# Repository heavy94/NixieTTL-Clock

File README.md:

# NixieTTL Clock
Tabletop digital clock built using TTL/CMOS logic ICs with a Nixie tube display.

**TODO**
- PCB layout and design.
- Test High Voltage power supply.
- Test need for base resistor on the cathode drivers.
- Test and tune blanking time generator.

**References**

This design is inspired by the following projects and resources:
- https://0x7d.com/2017/nixie-tube-clock/
- https://threeneurons.wordpress.com/nixie-power-supply/nixie-clock-kit-microcontroller/
- https://threeneurons.wordpress.com/nixie-power-supply/nixie-clock-kit-microcontroller/ghosting-due-to-transients/
- https://threeneurons.wordpress.com/nixie-power-supply/hv-supply-kit/

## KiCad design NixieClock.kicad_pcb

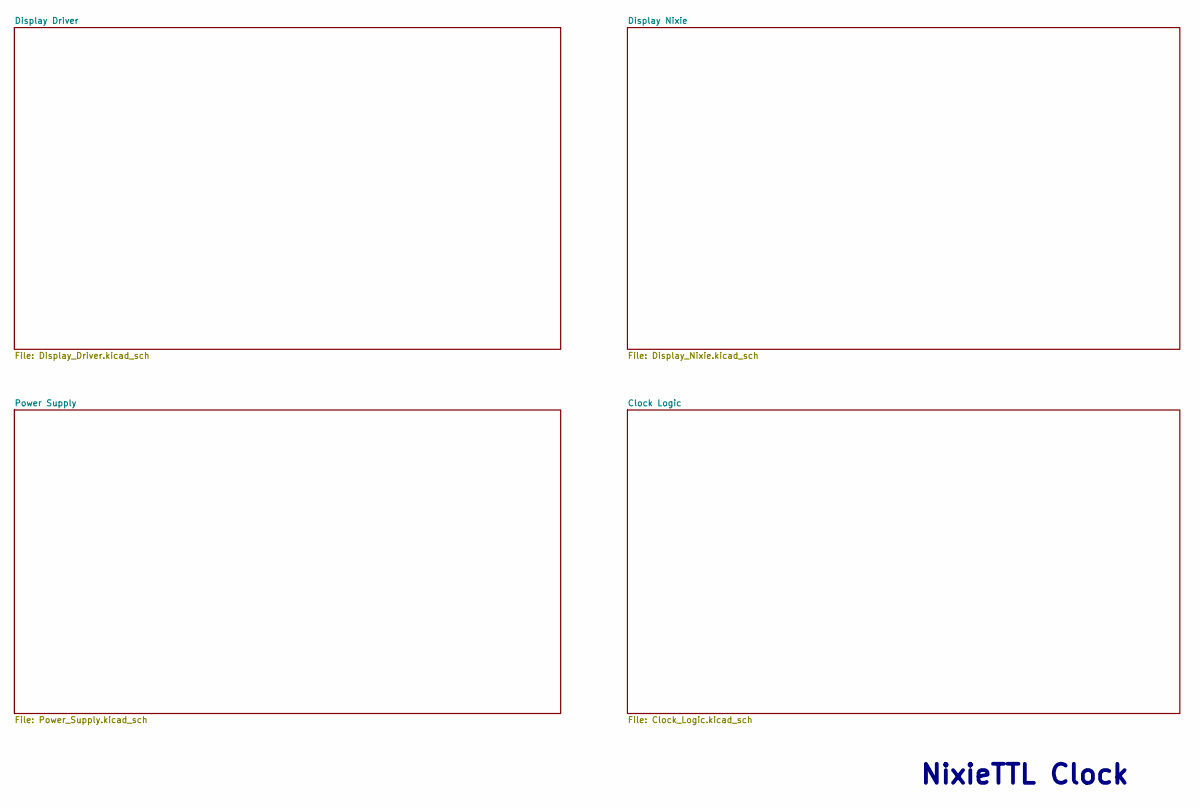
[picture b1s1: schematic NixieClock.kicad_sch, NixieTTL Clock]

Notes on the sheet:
NixieTTL Clock

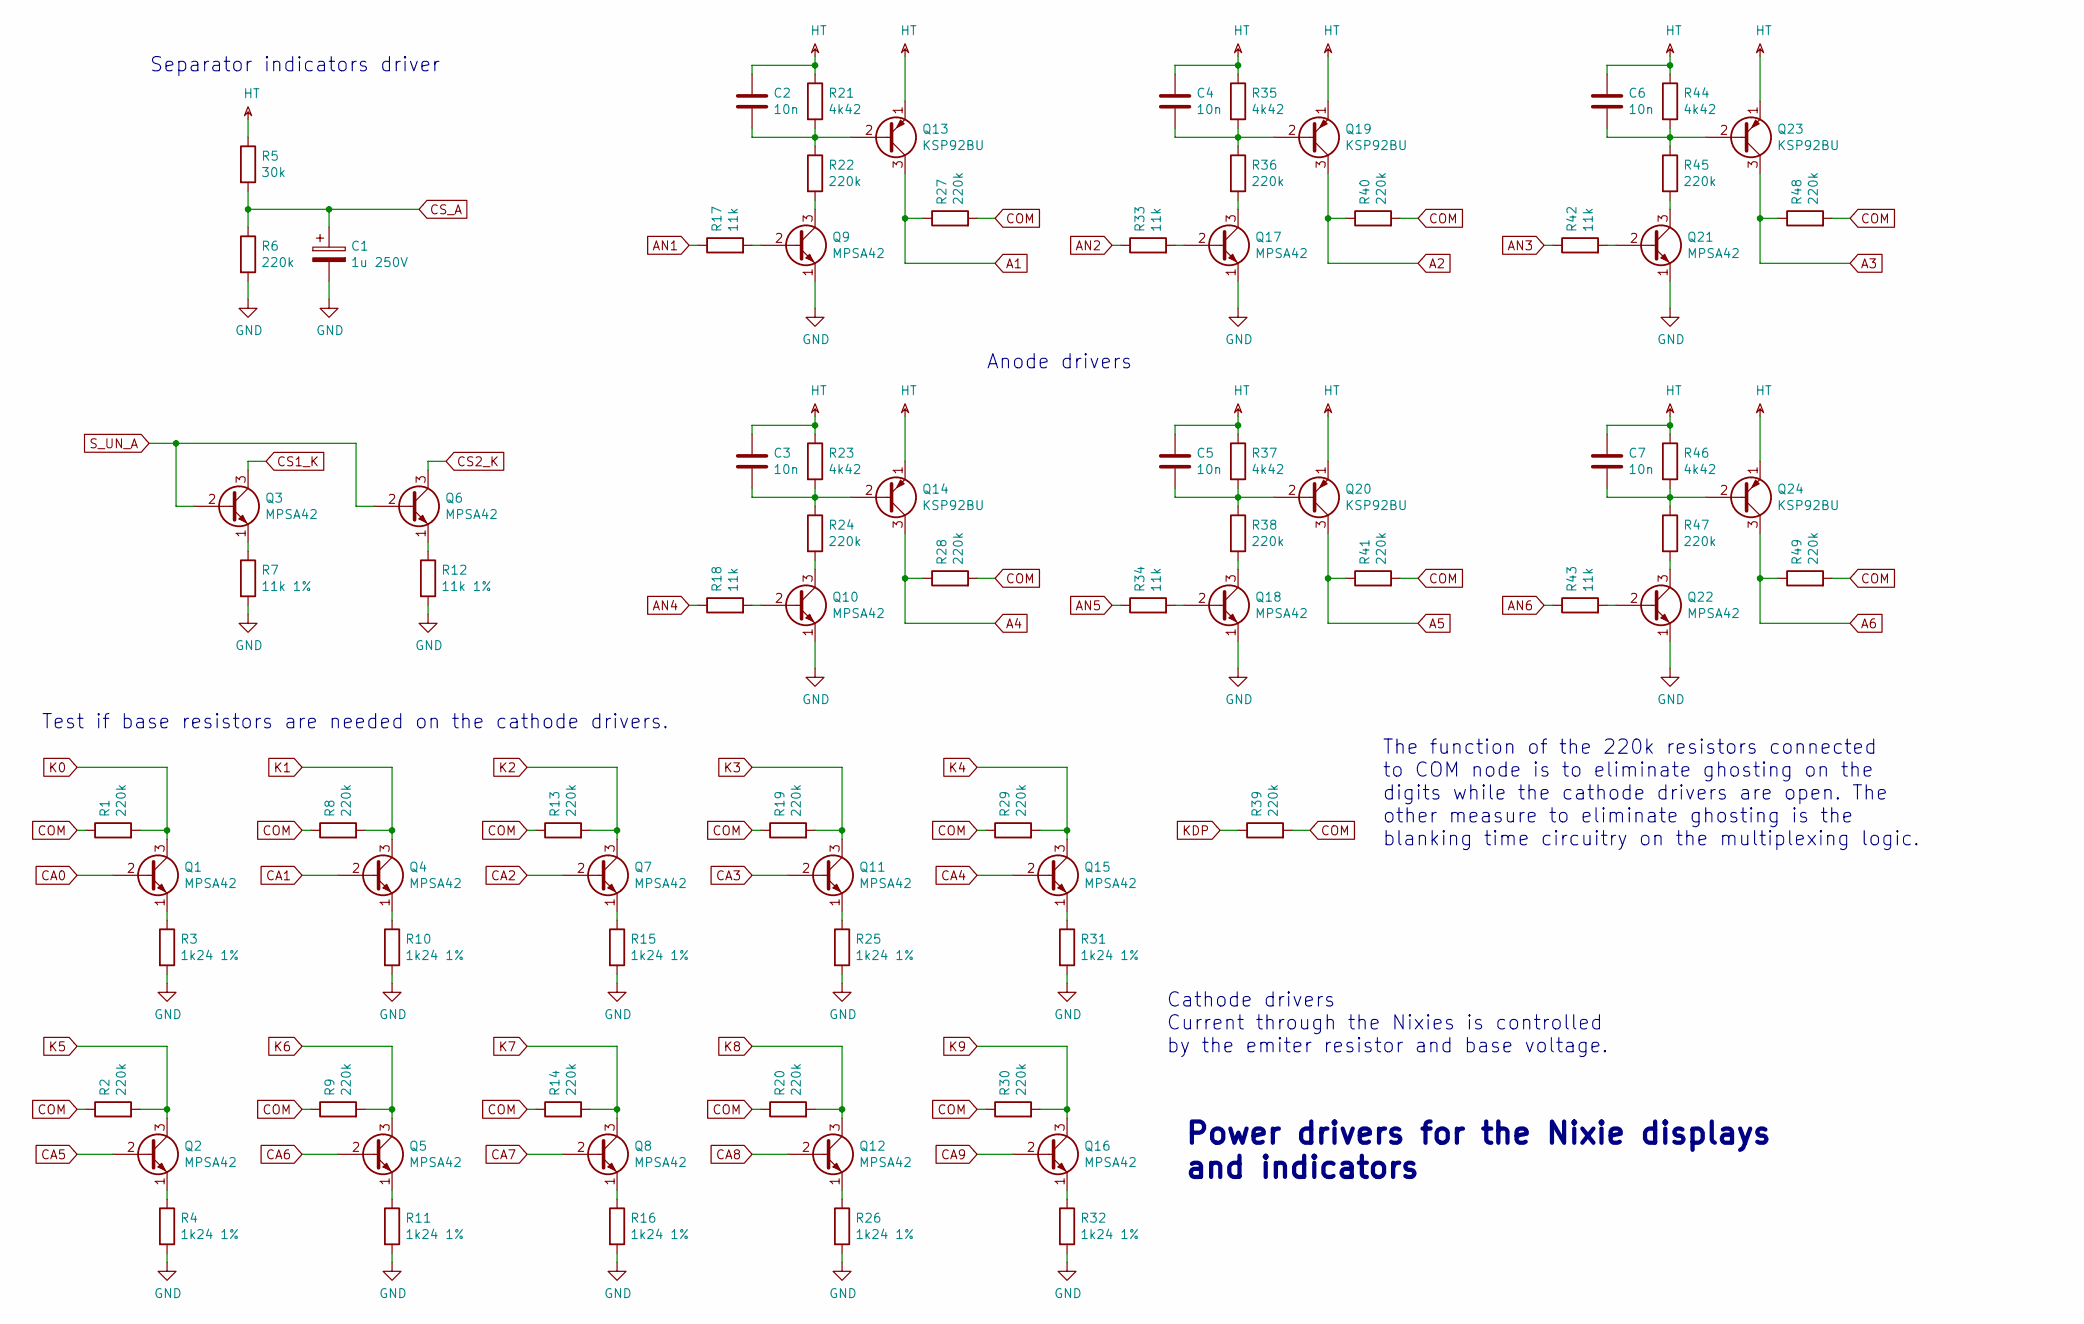
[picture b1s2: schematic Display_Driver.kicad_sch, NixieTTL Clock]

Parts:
C1: 1u 250V; CP_Radial_D8.0mm_P3.80mm
C2, C3, C4, C5, C6, C7: 10n; C_Rect_L7.0mm_W2.5mm_P5.00mm
Q1, Q2, Q3, Q4, Q5, Q6, Q7, Q8, Q9, Q10, Q11, Q12, Q15, Q16, Q17, Q18, Q21, Q22: MPSA42; TO-92_Inline_Wide
Q13, Q14, Q19, Q20, Q23, Q24: KSP92BU; TO-92_Inline_Wide
R1, R2, R6, R8, R9, R13, R14, R19, R20, R22, R24, R27, R28, R29, R30, R36, R38, R39, R40, R41, R45, R47, R48, R49: 220k; R_Axial_DIN0207_L6.3mm_D2.5mm_P10.16mm_Horizontal
R3, R4, R10, R11, R15, R16, R25, R26, R31, R32: 1k24 1%; R_Axial_DIN0207_L6.3mm_D2.5mm_P10.16mm_Horizontal
R5: 30k; R_Axial_DIN0207_L6.3mm_D2.5mm_P10.16mm_Horizontal
R7, R12: 11k 1%; R_Axial_DIN0207_L6.3mm_D2.5mm_P10.16mm_Horizontal
R17, R18, R33, R34, R42, R43: 11k; R_Axial_DIN0207_L6.3mm_D2.5mm_P10.16mm_Horizontal
R21, R23, R35, R37, R44, R46: 4k42; R_Axial_DIN0207_L6.3mm_D2.5mm_P10.16mm_Horizontal

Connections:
A1: Q13.3 (C), R27.1; also elsewhere on the board
A2: Q19.3 (C), R40.1; also elsewhere on the board
A3: Q23.3 (C), R48.1; also elsewhere on the board
A4: Q14.3 (C), R28.1; also elsewhere on the board
A5: Q20.3 (C), R41.1; also elsewhere on the board
A6: Q24.3 (C), R49.1; also elsewhere on the board
AN1: R17.1; also elsewhere on the board
AN2: R33.1; also elsewhere on the board
AN3: R42.1; also elsewhere on the board
AN4: R18.1; also elsewhere on the board
AN5: R34.1; also elsewhere on the board
AN6: R43.1; also elsewhere on the board
CA0: Q1.2 (B); also elsewhere on the board
CA1: Q4.2 (B); also elsewhere on the board
CA2: Q7.2 (B); also elsewhere on the board
CA3: Q11.2 (B); also elsewhere on the board
CA4: Q15.2 (B); also elsewhere on the board
CA5: Q2.2 (B); also elsewhere on the board
CA6: Q5.2 (B); also elsewhere on the board
CA7: Q8.2 (B); also elsewhere on the board
CA8: Q12.2 (B); also elsewhere on the board
CA9: Q16.2 (B); also elsewhere on the board
COM: R1.1, R2.1, R8.1, R9.1, R13.1, R14.1, R19.1, R20.1, R27.2, R28.2, R29.1, R30.1, R39.2, R40.2, R41.2, R48.2, R49.2
CS1_K: Q3.3 (C); also elsewhere on the board
CS2_K: Q6.3 (C); also elsewhere on the board
CS_A: C1.1, R5.2, R6.1; also elsewhere on the board
GND: C1.2, Q9.1 (E), Q10.1 (E), Q17.1 (E), Q18.1 (E), Q21.1 (E), Q22.1 (E), R3.2, R4.2, R6.2, R7.2, R10.2, R11.2, R12.2, R15.2, R16.2, R25.2, R26.2, R31.2, R32.2; also elsewhere on the board
HT: C2.1, C3.1, C4.1, C5.1, C6.1, C7.1, Q13.1 (E), Q14.1 (E), Q19.1 (E), Q20.1 (E), Q23.1 (E), Q24.1 (E), R5.1, R21.1, R23.1, R35.1, R37.1, R44.1, R46.1; also elsewhere on the board
K0: Q1.3 (C), R1.2; also elsewhere on the board
K1: Q4.3 (C), R8.2; also elsewhere on the board
K2: Q7.3 (C), R13.2; also elsewhere on the board
K3: Q11.3 (C), R19.2; also elsewhere on the board
K4: Q15.3 (C), R29.2; also elsewhere on the board
K5: Q2.3 (C), R2.2; also elsewhere on the board
K6: Q5.3 (C), R9.2; also elsewhere on the board
K7: Q8.3 (C), R14.2; also elsewhere on the board
K8: Q12.3 (C), R20.2; also elsewhere on the board
K9: Q16.3 (C), R30.2; also elsewhere on the board
KDP: R39.1; also elsewhere on the board
unnamed: C2.2, Q13.2 (B), R21.2, R22.1
unnamed: C3.2, Q14.2 (B), R23.2, R24.1
unnamed: C4.2, Q19.2 (B), R35.2, R36.1
unnamed: C5.2, Q20.2 (B), R37.2, R38.1
unnamed: C6.2, Q23.2 (B), R44.2, R45.1
unnamed: C7.2, Q24.2 (B), R46.2, R47.1
unnamed: Q1.1 (E), R3.1
unnamed: Q2.1 (E), R4.1
unnamed: Q3.1 (E), R7.1
unnamed: Q4.1 (E), R10.1
unnamed: Q5.1 (E), R11.1
unnamed: Q6.1 (E), R12.1
unnamed: Q7.1 (E), R15.1
unnamed: Q8.1 (E), R16.1
unnamed: Q9.2 (B), R17.2
unnamed: Q9.3 (C), R22.2
unnamed: Q10.2 (B), R18.2
unnamed: Q10.3 (C), R24.2
unnamed: Q11.1 (E), R25.1
unnamed: Q12.1 (E), R26.1
unnamed: Q15.1 (E), R31.1
unnamed: Q16.1 (E), R32.1
unnamed: Q17.2 (B), R33.2
unnamed: Q17.3 (C), R36.2
unnamed: Q18.2 (B), R34.2
unnamed: Q18.3 (C), R38.2
unnamed: Q21.2 (B), R42.2
unnamed: Q21.3 (C), R45.2
unnamed: Q22.2 (B), R43.2
unnamed: Q22.3 (C), R47.2
S_UN_A: Q3.2 (B), Q6.2 (B); also elsewhere on the board

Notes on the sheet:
Test if base resistors are needed on the cathode drivers.
The function of the 220k resistors connected to COM node is to eliminate ghosting on the digits while the cathode drivers are open. The other measure to eliminate ghosting is the blanking time circuitry on the multiplexing logic.
Separator indicators driver
Power drivers for the Nixie displays and indicators
Cathode drivers Current through the Nixies is controlled by the emiter resistor and base voltage.
Anode drivers

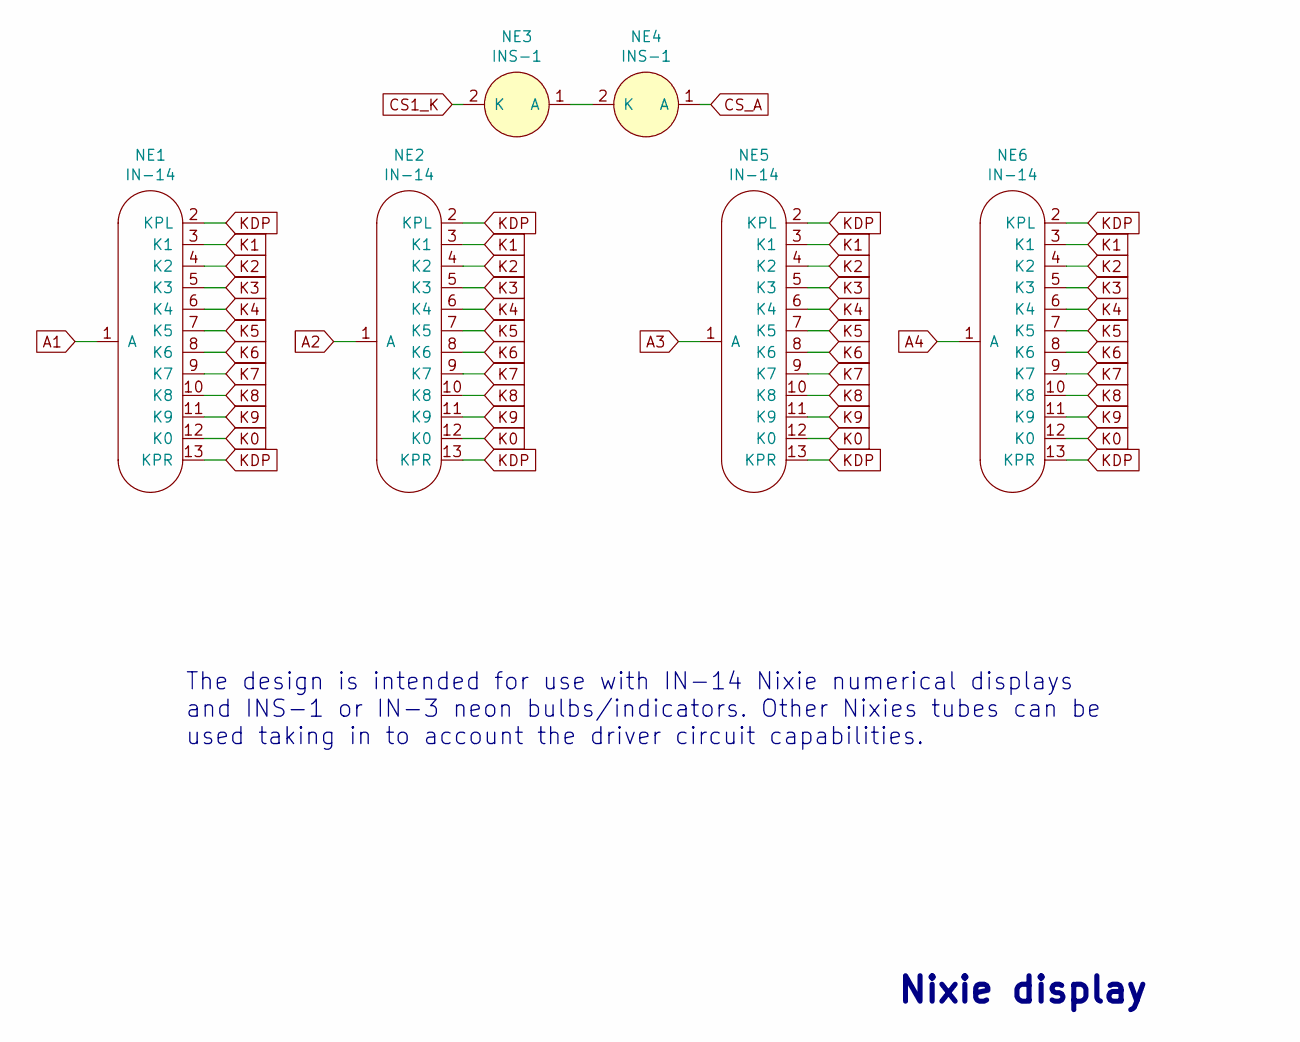
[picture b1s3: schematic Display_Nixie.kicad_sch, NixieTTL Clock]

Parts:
NE1, NE2, NE5, NE6: IN-14
NE3, NE4: INS-1; PinSocket_1x02_P2.54mm_Vertical

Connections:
A1: NE1.1 (A); also elsewhere on the board
A2: NE2.1 (A); also elsewhere on the board
A3: NE5.1 (A); also elsewhere on the board
A4: NE6.1 (A); also elsewhere on the board
CS1_K: NE3.2 (K); also elsewhere on the board
CS_A: NE4.1 (A); also elsewhere on the board
K0: NE1.12 (K0), NE2.12 (K0), NE5.12 (K0), NE6.12 (K0); also elsewhere on the board
K1: NE1.3 (K1), NE2.3 (K1), NE5.3 (K1), NE6.3 (K1); also elsewhere on the board
K2: NE1.4 (K2), NE2.4 (K2), NE5.4 (K2), NE6.4 (K2); also elsewhere on the board
K3: NE1.5 (K3), NE2.5 (K3), NE5.5 (K3), NE6.5 (K3); also elsewhere on the board
K4: NE1.6 (K4), NE2.6 (K4), NE5.6 (K4), NE6.6 (K4); also elsewhere on the board
K5: NE1.7 (K5), NE2.7 (K5), NE5.7 (K5), NE6.7 (K5); also elsewhere on the board
K6: NE1.8 (K6), NE2.8 (K6), NE5.8 (K6), NE6.8 (K6); also elsewhere on the board
K7: NE1.9 (K7), NE2.9 (K7), NE5.9 (K7), NE6.9 (K7); also elsewhere on the board
K8: NE1.10 (K8), NE2.10 (K8), NE5.10 (K8), NE6.10 (K8); also elsewhere on the board
K9: NE1.11 (K9), NE2.11 (K9), NE5.11 (K9), NE6.11 (K9); also elsewhere on the board
KDP: NE1.2 (KPL), NE1.13 (KPR), NE2.2 (KPL), NE2.13 (KPR), NE5.2 (KPL), NE5.13 (KPR), NE6.2 (KPL), NE6.13 (KPR); also elsewhere on the board
unnamed: NE3.1 (A), NE4.2 (K)

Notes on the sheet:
Nixie display
The design is intended for use with IN-14 Nixie numerical displays and INS-1 or IN-3 neon bulbs/indicators. Other Nixies tubes can be used taking in to account the driver circuit capabilities.

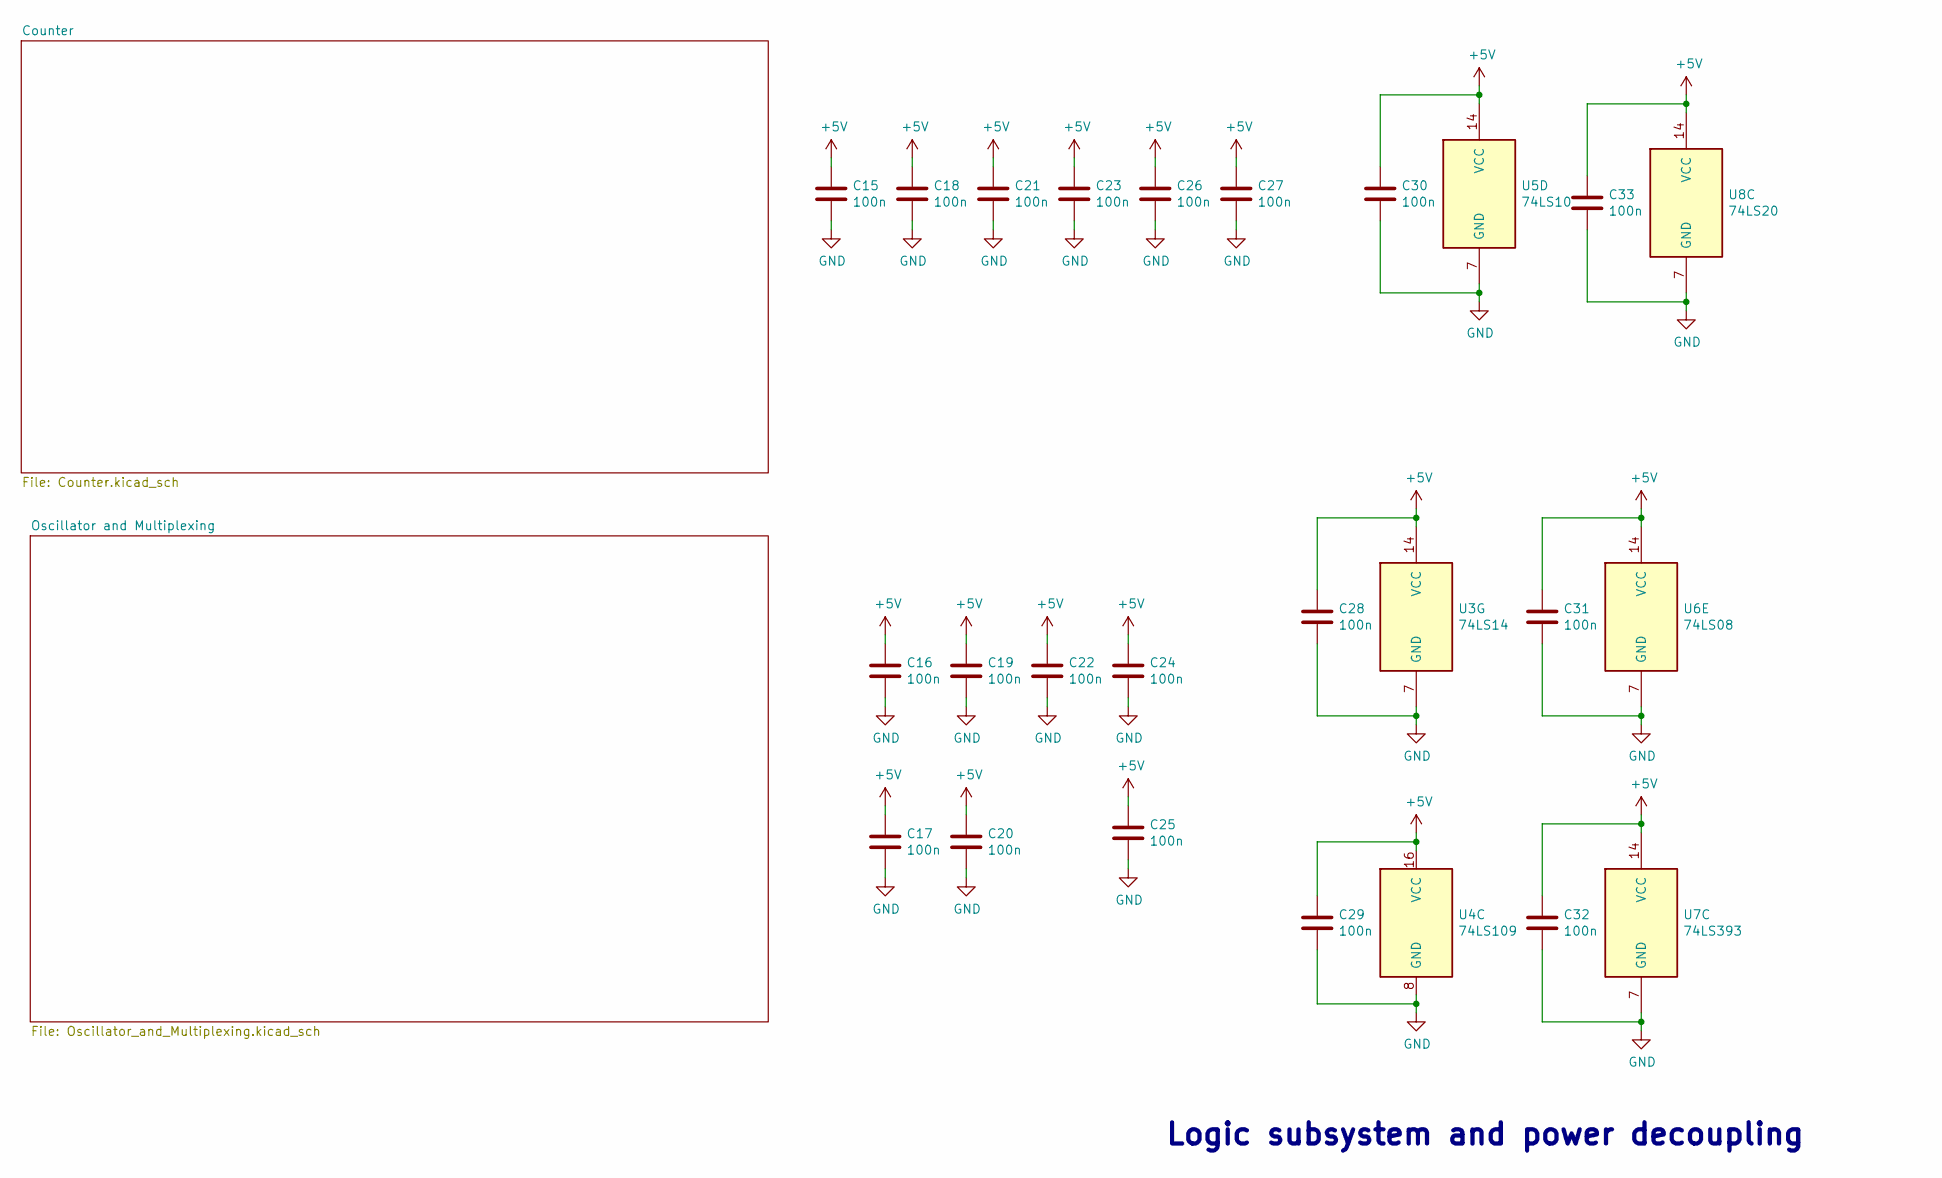
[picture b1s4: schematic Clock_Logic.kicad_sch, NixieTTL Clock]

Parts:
C15, C16, C17, C18, C19, C20, C21, C22, C23, C24, C25, C26, C27, C28, C29, C30, C31, C32, C33: 100n; C_Rect_L7.0mm_W2.5mm_P5.00mm
U3: 74LS14; DIP-14_W7.62mm
U4: 74LS109; DIP-16_W7.62mm
U5: 74LS10; DIP-14_W7.62mm
U6: 74LS08; DIP-14_W7.62mm
U7: 74LS393; DIP-14_W7.62mm
U8: 74LS20; DIP-14_W7.62mm

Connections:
+5V: C15.1, C16.1, C17.1, C18.1, C19.1, C20.1, C21.1, C22.1, C23.1, C24.1, C25.1, C26.1, C27.1, C28.1, C29.1, C30.1, C31.1, C32.1, C33.1, U3.14 (VCC), U4.16 (VCC), U5.14 (VCC), U6.14 (VCC), U7.14 (VCC), U8.14 (VCC); also elsewhere on the board
GND: C15.2, C16.2, C17.2, C18.2, C19.2, C20.2, C21.2, C22.2, C23.2, C24.2, C25.2, C26.2, C27.2, C28.2, C29.2, C30.2, C31.2, C32.2, C33.2, U3.7 (GND), U4.8 (GND), U5.7 (GND), U6.7 (GND), U7.7 (GND), U8.7 (GND); also elsewhere on the board

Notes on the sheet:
Logic subsystem and power decoupling

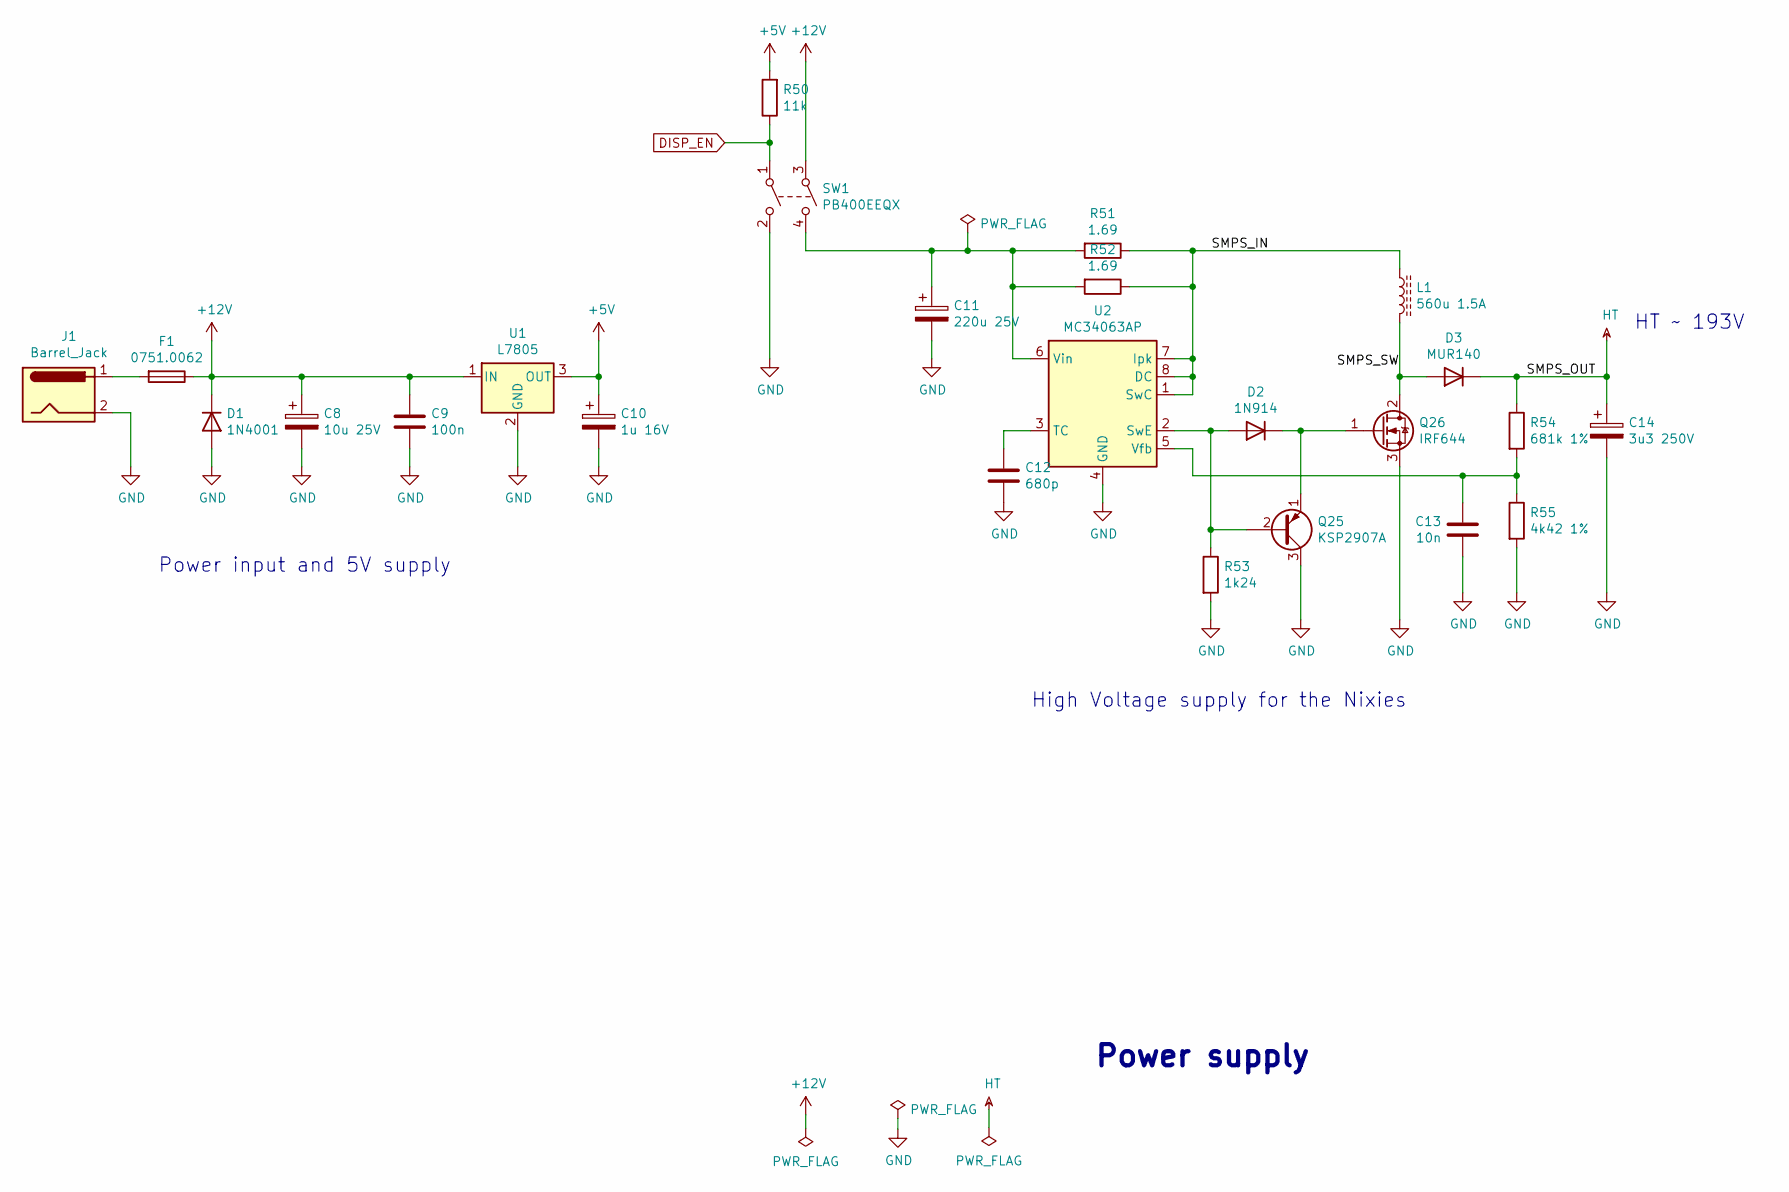
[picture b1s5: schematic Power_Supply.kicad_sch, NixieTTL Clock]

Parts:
C8: 10u 25V; CP_Radial_D5.0mm_P2.50mm
C9: 100n; C_Rect_L7.0mm_W2.5mm_P5.00mm
C10: 1u 16V; CP_Radial_D5.0mm_P2.50mm
C11: 220u 25V; CP_Radial_D8.0mm_P3.80mm
C12: 680p; C_Rect_L7.0mm_W4.5mm_P5.00mm
C13: 10n; C_Rect_L7.0mm_W2.5mm_P5.00mm
C14: 3u3 250V; CP_Radial_D8.0mm_P3.80mm
D1: 1N4001; D_DO-41_SOD81_P10.16mm_Horizontal
D2: 1N914; D_DO-35_SOD27_P7.62mm_Horizontal
D3: MUR140; D_DO-41_SOD81_P7.62mm_Horizontal
F1: 0751.0062; 5x20 fuse
J1: Barrel_Jack; BarrelJack_Horizontal
L1: 560u 1.5A; L_Radial_D12.0mm_P6.00mm_MuRATA_1900R
Q25: KSP2907A; TO-92_Inline_Wide
Q26: IRF644; TO-220-3_Vertical
R50: 11k; R_Axial_DIN0207_L6.3mm_D2.5mm_P10.16mm_Horizontal
R51, R52: 1.69; R_Axial_DIN0207_L6.3mm_D2.5mm_P10.16mm_Horizontal
R53: 1k24; R_Axial_DIN0207_L6.3mm_D2.5mm_P10.16mm_Horizontal
R54: 681k 1%; R_Axial_DIN0207_L6.3mm_D2.5mm_P10.16mm_Horizontal
R55: 4k42 1%; R_Axial_DIN0207_L6.3mm_D2.5mm_P10.16mm_Horizontal
SW1: PB400EEQX
U1: L7805; TO-220-3_Vertical
U2: MC34063AP; DIP-8_W7.62mm

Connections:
+5V: C10.1, R50.2, U1.3 (OUT); also elsewhere on the board
+12V: C8.1, C9.1, D1.1 (K), F1.1, SW1.3, U1.1 (IN)
/Power Supply/SMPS_IN: L1.1, R51.1, R52.1, U2.1 (SwC), U2.7 (Ipk), U2.8 (DC)
/Power Supply/SMPS_SW: D3.2 (A), L1.2, Q26.2 (D)
DISP_EN: R50.1, SW1.1; also elsewhere on the board
GND: C8.2, C9.2, C10.2, C11.2, C12.2, C13.2, C14.2, D1.2 (A), J1.2, Q25.3 (C), Q26.3 (S), R53.2, R55.2, SW1.2, U1.2 (GND), U2.4 (GND); also elsewhere on the board
HT: C14.1, D3.1 (K), R54.1; also elsewhere on the board
unnamed: C11.1, R51.2, R52.2, SW1.4, U2.6 (Vin)
unnamed: C12.1, U2.3 (TC)
unnamed: C13.1, R54.2, R55.1, U2.5 (Vfb)
unnamed: D2.1 (K), Q25.1 (E), Q26.1 (G)
unnamed: D2.2 (A), Q25.2 (B), R53.1, U2.2 (SwE)
unnamed: F1.2, J1.1

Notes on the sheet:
Power supply
Power input and 5V supply
High Voltage supply for the Nixies
HT ~ 193V

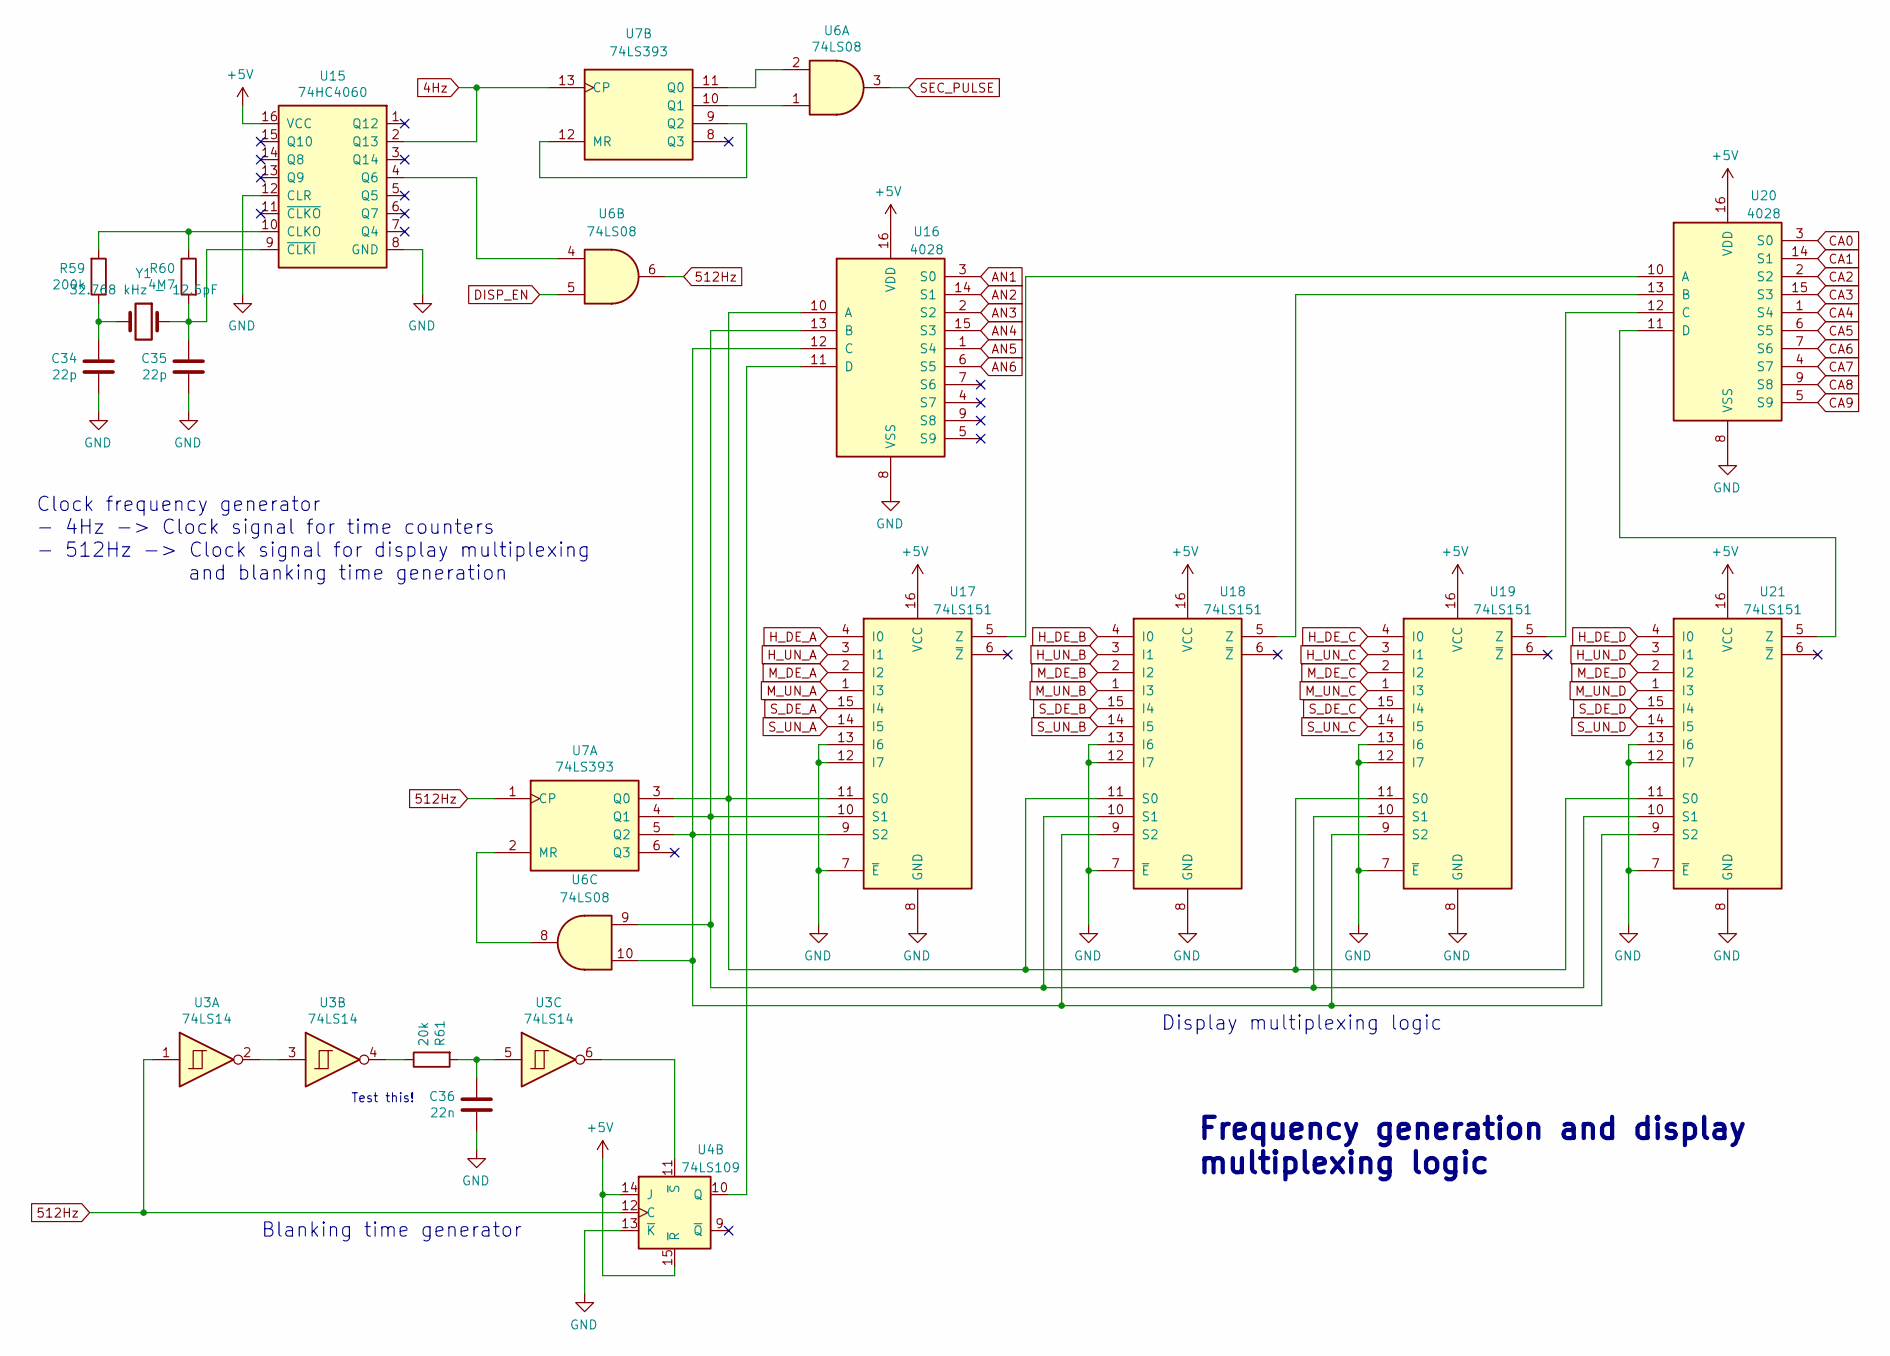
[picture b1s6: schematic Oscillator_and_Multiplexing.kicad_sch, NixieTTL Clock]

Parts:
C34, C35: 22p; C_Disc_D5.1mm_W3.2mm_P5.00mm
C36: 22n; C_Rect_L7.0mm_W2.5mm_P5.00mm
R59: 200k; R_Axial_DIN0207_L6.3mm_D2.5mm_P10.16mm_Horizontal
R60: 4M7; R_Axial_DIN0207_L6.3mm_D2.5mm_P10.16mm_Horizontal
R61: 20k; R_Axial_DIN0207_L6.3mm_D2.5mm_P10.16mm_Horizontal
U3: 74LS14; DIP-14_W7.62mm
U4: 74LS109; DIP-16_W7.62mm
U6: 74LS08; DIP-14_W7.62mm
U7: 74LS393; DIP-14_W7.62mm
U15: 74HC4060; DIP-16_W7.62mm
U16, U20: 4028; DIP-16_W7.62mm
U17, U18, U19, U21: 74LS151; DIP-16_W7.62mm
Y1: 32.768 kHz - 12.5pF; Crystal_C38-LF_D3.0mm_L8.0mm_Vertical

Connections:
4Hz: U7.13 (CP), U15.2 (Q13); also elsewhere on the board
512Hz: U3.1, U4.12 (C), U6.6, U7.1 (CP)
+5V: U4.14 (J), U4.15 (~R), U15.16 (VCC), U16.16 (VDD), U17.16 (VCC), U18.16 (VCC), U19.16 (VCC), U20.16 (VDD), U21.16 (VCC); also elsewhere on the board
AN1: U16.3 (S0); also elsewhere on the board
AN2: U16.14 (S1); also elsewhere on the board
AN3: U16.2 (S2); also elsewhere on the board
AN4: U16.15 (S3); also elsewhere on the board
AN5: U16.1 (S4); also elsewhere on the board
AN6: U16.6 (S5); also elsewhere on the board
CA0: U20.3 (S0); also elsewhere on the board
CA1: U20.14 (S1); also elsewhere on the board
CA2: U20.2 (S2); also elsewhere on the board
CA3: U20.15 (S3); also elsewhere on the board
CA4: U20.1 (S4); also elsewhere on the board
CA5: U20.6 (S5); also elsewhere on the board
CA6: U20.7 (S6); also elsewhere on the board
CA7: U20.4 (S7); also elsewhere on the board
CA8: U20.9 (S8); also elsewhere on the board
CA9: U20.5 (S9); also elsewhere on the board
DISP_EN: U6.5; also elsewhere on the board
GND: C34.2, C35.2, C36.2, U4.13 (~K), U15.8 (GND), U15.12 (CLR), U16.8 (VSS), U17.7 (~E), U17.8 (GND), U17.12 (I7), U17.13 (I6), U18.7 (~E), U18.8 (GND), U18.12 (I7), U18.13 (I6), U19.7 (~E), U19.8 (GND), U19.12 (I7), U19.13 (I6), U20.8 (VSS), U21.7 (~E), U21.8 (GND), U21.12 (I7), U21.13 (I6); also elsewhere on the board
H_DE_A: U17.4 (I0); also elsewhere on the board
H_DE_B: U18.4 (I0); also elsewhere on the board
H_DE_C: U19.4 (I0); also elsewhere on the board
H_DE_D: U21.4 (I0); also elsewhere on the board
H_UN_A: U17.3 (I1); also elsewhere on the board
H_UN_B: U18.3 (I1); also elsewhere on the board
H_UN_C: U19.3 (I1); also elsewhere on the board
H_UN_D: U21.3 (I1); also elsewhere on the board
M_DE_A: U17.2 (I2); also elsewhere on the board
M_DE_B: U18.2 (I2); also elsewhere on the board
M_DE_C: U19.2 (I2); also elsewhere on the board
M_DE_D: U21.2 (I2); also elsewhere on the board
M_UN_A: U17.1 (I3); also elsewhere on the board
M_UN_B: U18.1 (I3); also elsewhere on the board
M_UN_C: U19.1 (I3); also elsewhere on the board
M_UN_D: U21.1 (I3); also elsewhere on the board
unnamed: C34.1, R59.1, Y1.2
unnamed: C35.1, R60.2, U15.9 (~CLKI), Y1.1
unnamed: C36.1, R61.2, U3.5
unnamed: R59.2, R60.1, U15.10 (CLKO)
unnamed: R61.1, U3.4
unnamed: U3.2, U3.3
unnamed: U3.6, U4.11 (~S)
unnamed: U6.1, U7.10 (Q1)
unnamed: U6.2, U7.11 (Q0)
unnamed: U6.8, U7.2 (MR)
unnamed: U7.9 (Q2), U7.12 (MR)
unnamed: U6.4, U15.4 (Q6)
unnamed: U7.3 (Q0), U16.10 (A), U17.11 (S0), U18.11 (S0), U19.11 (S0), U21.11 (S0)
unnamed: U4.10 (Q), U16.11 (D)
unnamed: U6.10, U7.5 (Q2), U16.12 (C), U17.9 (S2), U18.9 (S2), U19.9 (S2), U21.9 (S2)
unnamed: U6.9, U7.4 (Q1), U16.13 (B), U17.10 (S1), U18.10 (S1), U19.10 (S1), U21.10 (S1)
unnamed: U17.5 (Z), U20.10 (A)
unnamed: U18.5 (Z), U20.13 (B)
unnamed: U19.5 (Z), U20.12 (C)
unnamed: U20.11 (D), U21.5 (Z)
SEC_PULSE: U6.3; also elsewhere on the board
S_DE_A: U17.15 (I4); also elsewhere on the board
S_DE_B: U18.15 (I4); also elsewhere on the board
S_DE_C: U19.15 (I4); also elsewhere on the board
S_DE_D: U21.15 (I4); also elsewhere on the board
S_UN_A: U17.14 (I5); also elsewhere on the board
S_UN_B: U18.14 (I5); also elsewhere on the board
S_UN_C: U19.14 (I5); also elsewhere on the board
S_UN_D: U21.14 (I5); also elsewhere on the board

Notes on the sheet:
Clock frequency generator - 4Hz -> Clock signal for time counters - 512Hz -> Clock signal for display multiplexing and blanking time generation
Display multiplexing logic
Test this!
Blanking time generator
Frequency generation and display multiplexing logic
